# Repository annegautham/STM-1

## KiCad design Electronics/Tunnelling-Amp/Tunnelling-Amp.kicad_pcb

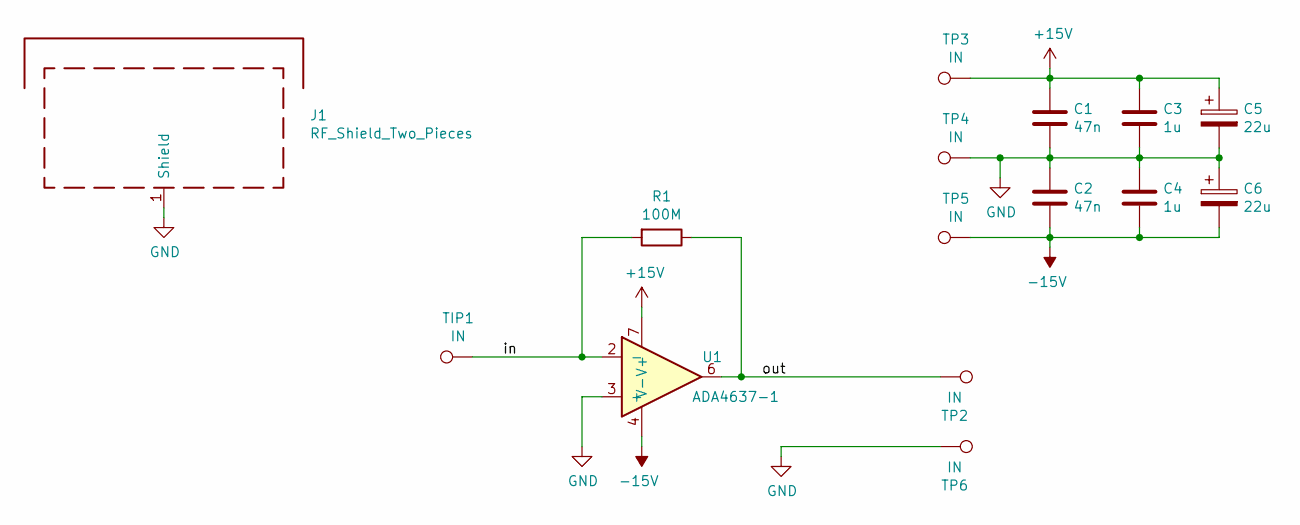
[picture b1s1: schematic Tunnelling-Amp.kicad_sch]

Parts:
C1, C2: 47n; C_0603_1608Metric_Pad1.05x0.95mm_HandSolder
C3, C4: 1u; C_0805_2012Metric_Pad1.15x1.40mm_HandSolder
C5, C6: 22u; CP_Elec_6.3x5.4
J1: RF_Shield_Two_Pieces; Laird_Technologies_BMI-S-101_13.66x12.70mm; Digikey 903-1006-1-ND
R1: 100M; R_1206_3216Metric_Pad1.42x1.75mm_HandSolder; Digikey 541-100MALCT-ND
TIP1: IN; TestPoint_Pad_2.5x2.5mm
TP2, TP3, TP4, TP5, TP6: IN; TestPoint_Pad_D3.0mm
U1: ADA4637-1; SOIC-8_3.9x4.9mm_P1.27mm; Digikey ADA4637-1ARZ-ND

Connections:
+15V: C1.1, C3.1, C5.1, TP3.1, U1.7 (V+)
-15V: C2.2, C4.2, C6.2, TP5.1, U1.4 (V-)
/in: R1.2, TIP1.1, U1.2 (-)
/out: R1.1, TP2.1, U1.6
GND: C1.2, C2.1, C3.2, C4.1, C5.2, C6.1, J1.1, TP4.1, TP6.1, U1.3 (+)

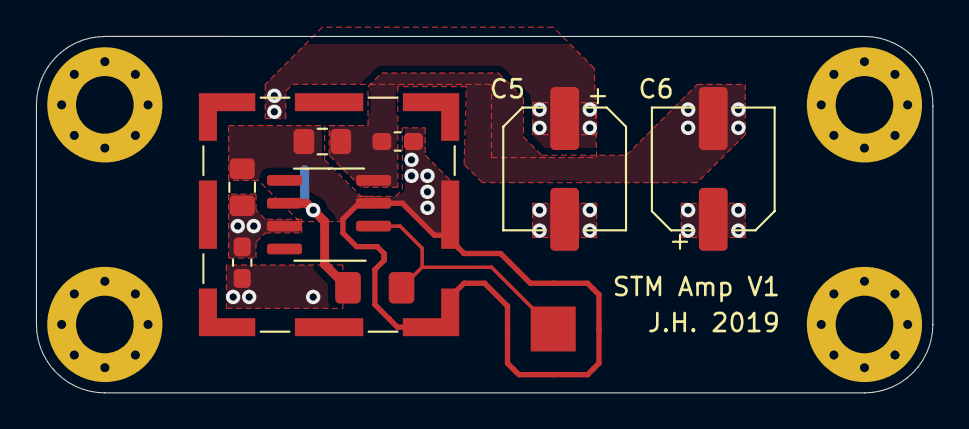
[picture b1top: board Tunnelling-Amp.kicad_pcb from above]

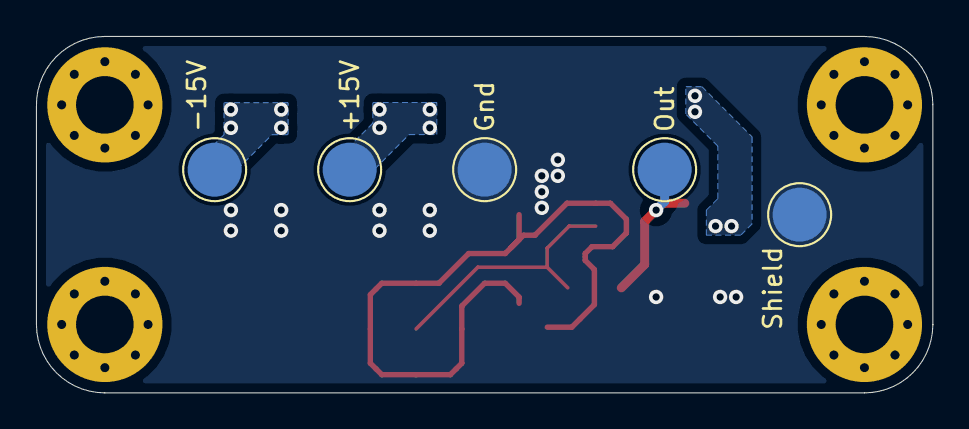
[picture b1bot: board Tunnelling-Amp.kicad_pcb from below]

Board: 2 copper layers, 49.8 x 19.8 mm, 15 parts (5 on the bottom side), 5 nets.

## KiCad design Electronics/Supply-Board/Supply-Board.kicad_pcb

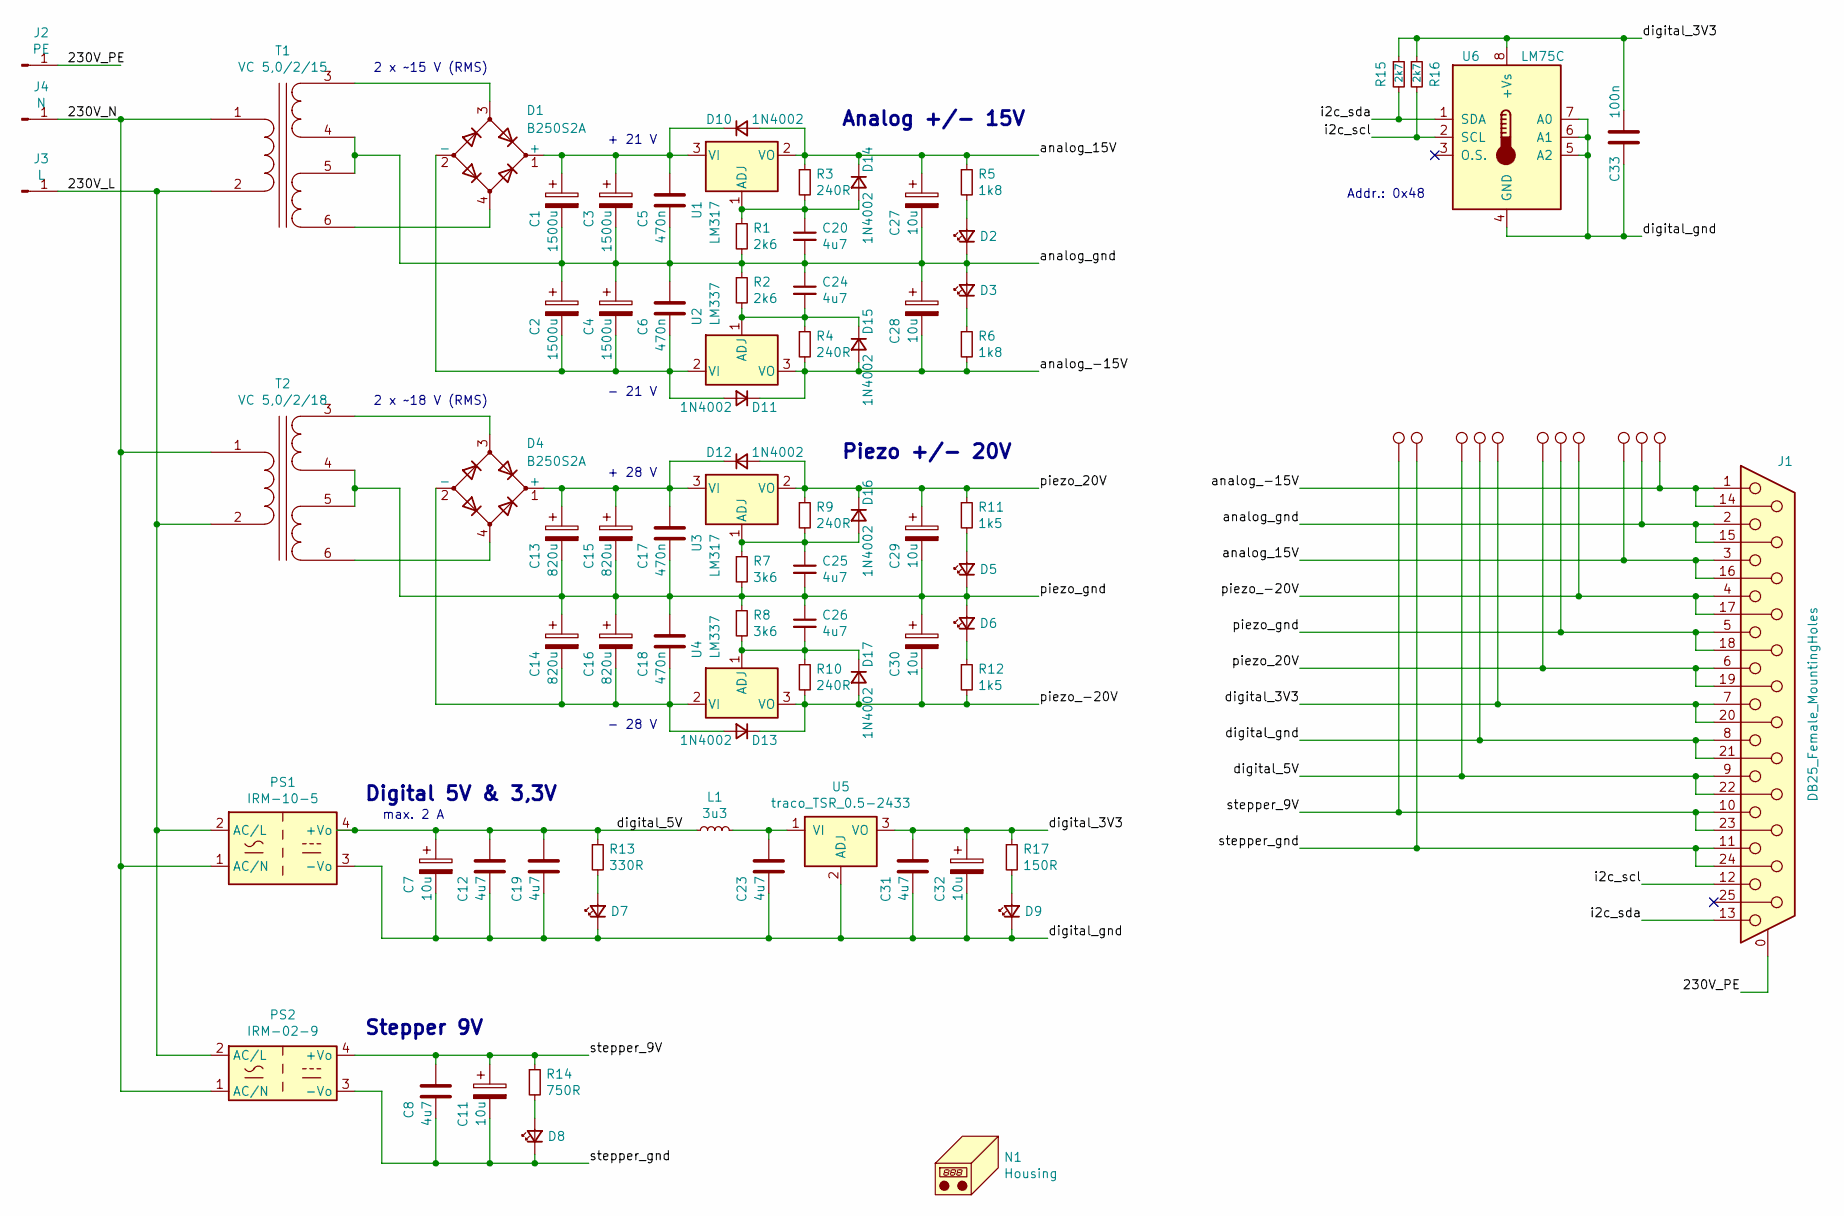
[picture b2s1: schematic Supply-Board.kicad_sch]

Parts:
C1, C2, C3, C4: 1500u; CP_Radial_D12.5mm_P5.00mm
C5, C6, C17, C18: 470n; C_1206_3216Metric_Pad1.42x1.75mm_HandSolder
C7, C11, C32: 10u; CP_EIA-6032-28_Kemet-C_Pad2.25x2.35mm_HandSolder
C8, C12, C19, C23, C31: 4u7; C_0805_2012Metric_Pad1.15x1.40mm_HandSolder
C13, C14, C15, C16: 820u; CP_Radial_D12.5mm_P5.00mm
C20, C24, C25, C26: 4u7; C_1206_3216Metric_Pad1.42x1.75mm_HandSolder
C27, C28, C29, C30: 10u; CP_EIA-7343-31_Kemet-D_Pad2.25x2.55mm_HandSolder
C33: 100n; C_0805_2012Metric_Pad1.15x1.40mm_HandSolder
D1, D4: B250S2A; Diode_Bridge_Diotec_SO-DIL-Slim
D2, D3, D5, D6, D7, D8, D9: LED_Small; LED_0603_1608Metric_Pad1.05x0.95mm_HandSolder
D10, D11, D12, D13, D14, D15, D16, D17: 1N4002; D_MELF
J1: DB25_Female_MountingHoles; DSUB-25_Female_Horizontal_P2.77x2.84mm_EdgePinOffset4.94mm_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
J2: PE; Pin_D1.3mm_L11.3mm_W2.8mm_Flat
J3: L; Pin_D1.3mm_L11.3mm_W2.8mm_Flat
J4: N; Pin_D1.3mm_L11.3mm_W2.8mm_Flat
L1: 3u3; L_Fastron_PISN_Handsoldering
N1: Housing; Hammond_1455N1602BK
PS1: IRM-10-5; Converter_ACDC_MeanWell_IRM-10-xx_THT
PS2: IRM-02-9; Converter_ACDC_MeanWell_IRM-02-xx_THT
R1, R2: 2k6; R_0805_2012Metric_Pad1.15x1.40mm_HandSolder
R3, R4, R9, R10: 240R; R_0805_2012Metric_Pad1.15x1.40mm_HandSolder
R5, R6: 1k8; R_0805_2012Metric_Pad1.15x1.40mm_HandSolder
R7, R8: 3k6; R_0805_2012Metric_Pad1.15x1.40mm_HandSolder
R11, R12: 1k5; R_0805_2012Metric_Pad1.15x1.40mm_HandSolder
R13: 330R; R_0805_2012Metric_Pad1.15x1.40mm_HandSolder
R14: 750R; R_0805_2012Metric_Pad1.15x1.40mm_HandSolder
R15, R16: 2k7; R_0805_2012Metric_Pad1.15x1.40mm_HandSolder
R17: 150R; R_0805_2012Metric_Pad1.15x1.40mm_HandSolder
T1: VC 5,0/2/15; Block_VC5
T2: VC 5,0/2/18; Block_VC5
TP1, TP2, TP3, TP4, TP5, TP6, TP7, TP8, TP9, TP10, TP11: TestPoint; TestPoint_Loop_D1.80mm_Drill1.0mm_Beaded
U1, U3: LM317; TO-252-2
U2, U4: LM337; TO-252-2
U5: traco_TSR_0.5-2433
U6: LM75C; SOIC-8_3.9x4.9mm_P1.27mm

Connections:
/230V_L: J3.1, PS1.2 (AC/L), PS2.2 (AC/L), T1.2 (AB), T2.2 (AB)
/230V_N: J4.1, PS1.1 (AC/N), PS2.1 (AC/N), T1.1 (AA), T2.1 (AA)
/230V_PE: J1.0 (PAD), J2.1
/analog_15V: C27.1, D10.2 (A), D14.1 (K), J1.3, J1.16, R3.1, R5.1, TP7.1, U1.2 (VO)
/analog_-15V: C28.2, D11.1 (K), D15.2 (A), J1.1, J1.14, R4.2, R6.2, TP1.1, U2.3 (VO)
/analog_gnd: C1.2, C2.1, C3.2, C4.1, C5.2, C6.1, C20.2, C24.1, C27.2, C28.1, D2.1 (K), D3.2 (A), J1.2, J1.15, R1.2, R2.1, T1.4 (SB), T1.5 (SC), TP8.1
/digital_3V3: C31.1, C32.1, C33.1, J1.7, J1.20, R15.1, R16.1, R17.1, TP3.1, U5.3 (VO), U6.8 (+Vs)
/digital_5V: C7.1, C12.1, C19.1, J1.9, J1.22, L1.1, PS1.4 (+Vo), R13.1, TP11.1
/digital_gnd: C7.2, C12.2, C19.2, C23.2, C31.2, C32.2, C33.2, D7.1 (K), D9.1 (K), J1.8, J1.21, PS1.3 (-Vo), TP2.1, U5.2 (ADJ), U6.4 (GND), U6.5 (A2), U6.6 (A1), U6.7 (A0)
/i2c_scl: J1.12, R16.2, U6.2 (SCL)
/i2c_sda: J1.13, R15.2, U6.1 (SDA)
/piezo_20V: C29.1, D12.2 (A), D16.1 (K), J1.6, J1.19, R9.1, R11.1, TP4.1, U3.2 (VO)
/piezo_-20V: C30.2, D13.1 (K), D17.2 (A), J1.4, J1.17, R10.2, R12.2, TP6.1, U4.3 (VO)
/piezo_gnd: C13.2, C14.1, C15.2, C16.1, C17.2, C18.1, C25.2, C26.1, C29.2, C30.1, D5.1 (K), D6.2 (A), J1.5, J1.18, R7.2, R8.1, T2.4 (SB), T2.5 (SC), TP5.1
/stepper_9V: C8.1, C11.1, J1.10, J1.23, PS2.4 (+Vo), R14.1, TP9.1
/stepper_gnd: C8.2, C11.2, D8.1 (K), J1.11, J1.24, PS2.3 (-Vo), TP10.1
unnamed: C1.1, C3.1, C5.1, D1.1 (+), D10.1 (K), U1.3 (VI)
unnamed: C2.2, C4.2, C6.2, D1.2 (-), D11.2 (A), U2.2 (VI)
unnamed: D2.2 (A), R5.2
unnamed: D3.1 (K), R6.1
unnamed: D5.2 (A), R11.2
unnamed: D6.1 (K), R12.1
unnamed: D7.2 (A), R13.2
unnamed: D8.2 (A), R14.2
unnamed: D9.2 (A), R17.2
unnamed: C13.1, C15.1, C17.1, D4.1 (+), D12.1 (K), U3.3 (VI)
unnamed: C14.2, C16.2, C18.2, D4.2 (-), D13.2 (A), U4.2 (VI)
unnamed: C20.1, D14.2 (A), R1.1, R3.2, U1.1 (ADJ)
unnamed: C24.2, D15.1 (K), R2.2, R4.1, U2.1 (ADJ)
unnamed: C25.1, D16.2 (A), R7.1, R9.2, U3.1 (ADJ)
unnamed: C26.2, D17.1 (K), R8.2, R10.1, U4.1 (ADJ)
unnamed: D1.3, T1.3 (SA)
unnamed: D1.4, T1.6 (SD)
unnamed: D4.3, T2.3 (SA)
unnamed: D4.4, T2.6 (SD)
unnamed: C23.1, L1.2, U5.1 (VI)

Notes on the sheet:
Piezo +/- 20V
max. 2 A
- 21 V
Stepper 9V
2 x ~18 V (RMS)
2 x ~15 V (RMS)
- 28 V
Digital 5V & 3,3V
Addr.: 0x48
+ 21 V
Analog +/- 15V
+ 28 V

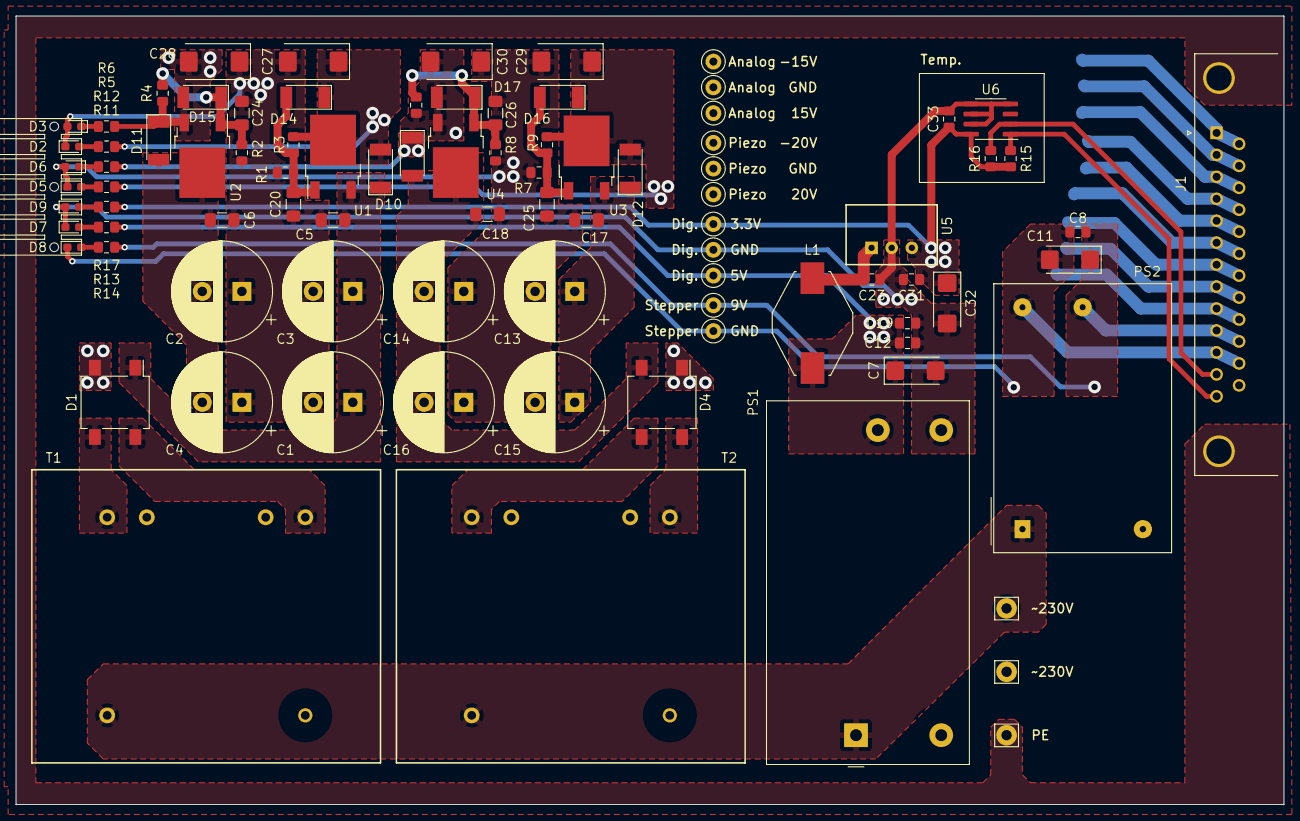
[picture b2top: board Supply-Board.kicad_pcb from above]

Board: 2 copper layers, 160.0 x 99.5 mm, 91 parts (0 on the bottom side), 36 nets.

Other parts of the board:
e: light-guide

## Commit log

2025-03-03 Power Supply Design Requirements
